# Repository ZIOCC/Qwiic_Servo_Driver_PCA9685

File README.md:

# Qwiic 16 Servo Driver (PCA9685)

> This product can be available for purchase [here](https://www.smart-prototyping.com/Zio-16-Servo-Controller.html).

#### Description

With the Zio 16-Channel 12 bit PWM controller, using the PCA9685 from NXP Semiconductors, you can control up to 16 servos or other PWM-controllable components using I2C.

Each output can be off or on (no PWM control), or set any channel to its own PWM frequency and duty cycle. The PCA9685 operates with a supply voltage range of 2.3v to 5.5v and both the inputs and outputs are 5.5v tolerant. Servos can be connected directly to output pins (up to 25 mA, 5.5v) or controlled with external drivers for more power-hungry applications. 

The board comes equipped with two Qwiic connectors to enable easy daisy-chaining. Need even more channels to control something like a hexapod robot? Quickly and easily connect another servo controller with the additional Qwiic connector and 6 solder-jumper configurable address bits. That means you can have up to 62 of these boards operating on the same I2C bus. You can also configure the boards to recognize group addresses, so that multiple boards can be controlled in parallel with a single command.

This is a derivative of Adafruit’s 16-Channel 12-bit PWM/Servo Driver - I2C interface - PCA9685, with the main difference being the addition of the Qwiic connectors. If you want to make Qwiic a regular part of your hardware hacking/making toolkit (we can’t image why you wouldn’t), this is the Servo Driver for you.

#### Specification

* 62 possible I2C addresses
* Weight: 8.0g (0.278oz)
* Dimension: 59.5x25.2 mm
* IC: PCA9685
* I2C address: 0x40-0x7F (default: 0x40)

#### Links

* [PCA9685 datasheet](https://www.smart-prototyping.com/image/data/NOA-RnD/101896%2016%20Servo%20Controller/PCA9685.pdf)
* [Adafruit PWM Servo Driver Library](https://github.com/adafruit/Adafruit-PWM-Servo-Driver-Library)
* [Example Code](https://www.smart-prototyping.com/image/data/NOA-RnD/101896%2016%20Servo%20Controller/2_servos.ino0)
* [Eagle files](https://github.com/ZIOCC/Qwiic_Servo_Driver_PCA9685)

Connections for Example Code, connecting two servos to the servo driver board. 

> ###### About Zio
> Zio is a new line of open sourced, compact, and grid layout boards, fully integrated for Arduino and Qwiic ecosystem. Designed ideally for wearables, robotics, small-space limitations or other on the go projects. Check out other awesome Zio products [here](https://www.smart-prototyping.com/Zio).

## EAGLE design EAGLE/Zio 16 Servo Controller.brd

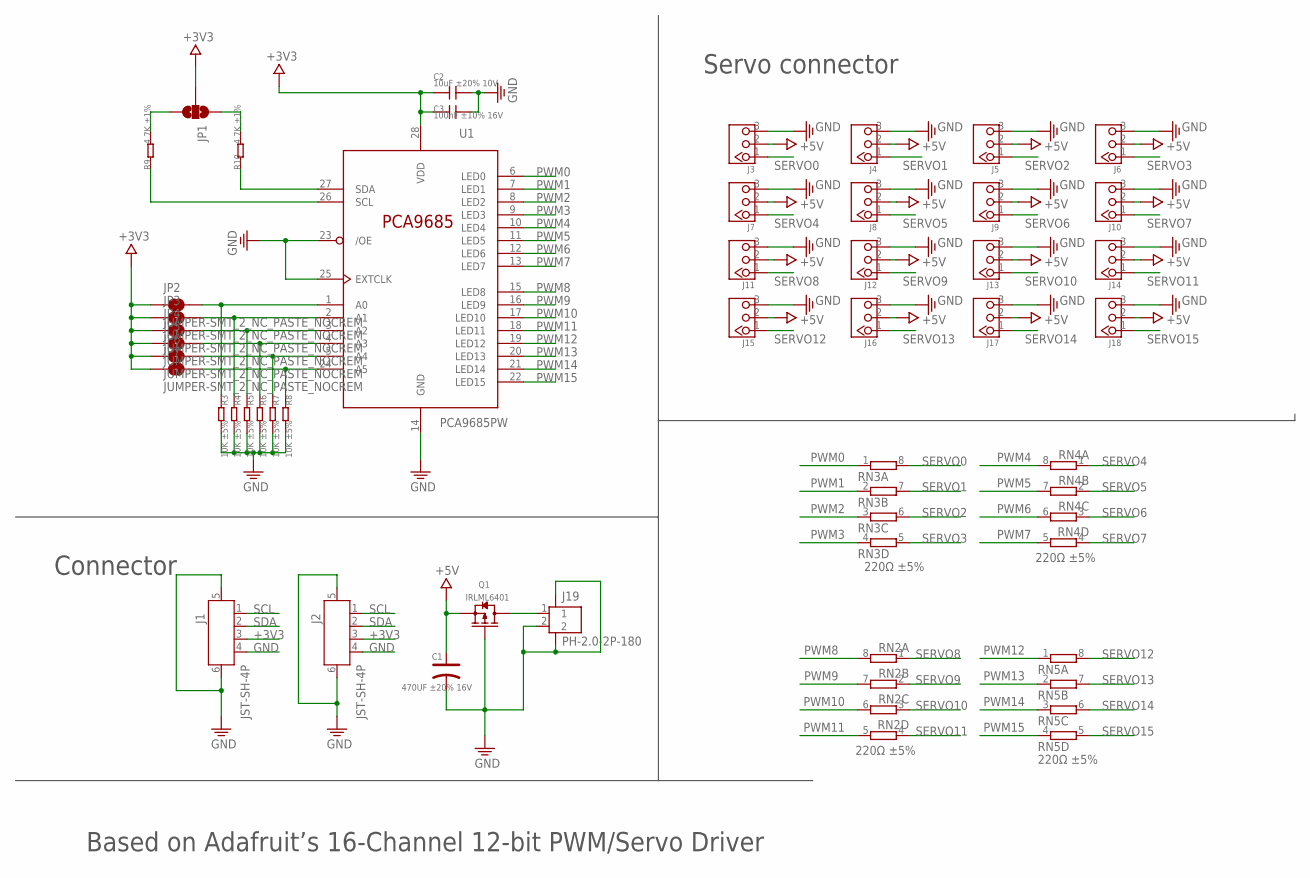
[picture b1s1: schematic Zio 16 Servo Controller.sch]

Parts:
C1: 470UF ±20% 16V; ELECTRO-SMD-E-7.8MM
C2: 10uF ±20% 10V; 0402
C3: 100nF ±10% 16V; 0402
J1, J2: JST-SH-4P; JST-SH-4P-90
J3, J4, J5, J6, J7, J8, J9, J10, J11, J12, J13, J14, J15, J16, J17, J18: HEADER-3P-2.54; 3P-2.54
J19: PH-2.0-2P-180; PH2.0_2P_180
JP1: JUMPER-SMT_3_2-NC_PASTE_NOCREM; SMT-JUMPER_3_2-NC_PASTE_SILK_NOCREM
JP2, JP3, JP4, JP5, JP6, JP7: JUMPER-SMT_2_NC_PASTE_NOCREM; SMT-JUMPER_2_NC_PASTE_SILK_NOCREM
Q1: IRLML6401; SOT23
R3, R4, R5, R6, R7, R8: 10K ±5%; 0402
R9, R10: 4.7K ±1%; 0402
RN2, RN3, RN4, RN5: 220Ω ±5%; RESISTOR-DIL_0603-ARV
U1: PCA9685PW; TSSOP28

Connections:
+3V3: C2.1, C3.1, J1.3, J2.3, JP1.2, JP2.1, JP3.1, JP4.1, JP5.1, JP6.1, JP7.1, U1.28 (VDD)
+5V: C1.+, J3.2, J4.2, J5.2, J6.2, J7.2, J8.2, J9.2, J10.2, J11.2, J12.2, J13.2, J14.2, J15.2, J16.2, J17.2, J18.2, Q1.2 (S)
GND: C1.-, C2.2, C3.2, J1.4, J1.5, J1.6, J2.4, J2.5, J2.6, J3.3, J4.3, J5.3, J6.3, J7.3, J8.3, J9.3, J10.3, J11.3, J12.3, J13.3, J14.3, J15.3, J16.3, J17.3, J18.3, J19.2, J19.3, J19.4, Q1.1 (G), R3.2, R4.2, R5.2, R6.2, R7.2, R8.2, U1.14 (GND), U1.23 (/OE), U1.25 (EXTCLK)
unnamed: JP2.2, R3.1, U1.1 (A0)
unnamed: JP3.2, R4.1, U1.2 (A1)
unnamed: JP4.2, R5.1, U1.3 (A2)
unnamed: JP5.2, R6.1, U1.4 (A3)
unnamed: JP6.2, R7.1, U1.5 (A4)
unnamed: JP7.2, R8.1, U1.24 (A5)
unnamed: J19.1, Q1.3 (D)
unnamed: JP1.3, R9.2
unnamed: JP1.1, R10.2
PWM0: RN3.1, U1.6 (LED0)
PWM1: RN3.2 (1), U1.7 (LED1)
PWM2: RN3.3 (1), U1.8 (LED2)
PWM3: RN3.4 (1), U1.9 (LED3)
PWM4: RN4.8 (2), U1.10 (LED4)
PWM5: RN4.7 (2), U1.11 (LED5)
PWM6: RN4.6 (2), U1.12 (LED6)
PWM7: RN4.5 (2), U1.13 (LED7)
PWM8: RN2.8 (2), U1.15 (LED8)
PWM9: RN2.7 (2), U1.16 (LED9)
PWM10: RN2.6 (2), U1.17 (LED10)
PWM11: RN2.5 (2), U1.18 (LED11)
PWM12: RN5.1, U1.19 (LED12)
PWM13: RN5.2 (1), U1.20 (LED13)
PWM14: RN5.3 (1), U1.21 (LED14)
PWM15: RN5.4 (1), U1.22 (LED15)
SCL: J1.1, J2.1, R9.1, U1.26 (SCL)
SDA: J1.2, J2.2, R10.1, U1.27 (SDA)
SERVO0: J3.1, RN3.8 (2)
SERVO1: J4.1, RN3.7 (2)
SERVO2: J5.1, RN3.6 (2)
SERVO3: J6.1, RN3.5 (2)
SERVO4: J7.1, RN4.1
SERVO5: J8.1, RN4.2 (1)
SERVO6: J9.1, RN4.3 (1)
SERVO7: J10.1, RN4.4 (1)
SERVO8: J11.1, RN2.1
SERVO9: J12.1, RN2.2 (1)
SERVO10: J13.1, RN2.3 (1)
SERVO11: J14.1, RN2.4 (1)
SERVO12: J15.1, RN5.8 (2)
SERVO13: J16.1, RN5.7 (2)
SERVO14: J17.1, RN5.6 (2)
SERVO15: J18.1, RN5.5 (2)

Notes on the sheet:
Servo connector
Connector
Based on Adafruit’s 16-Channel 12-bit PWM/Servo Driver

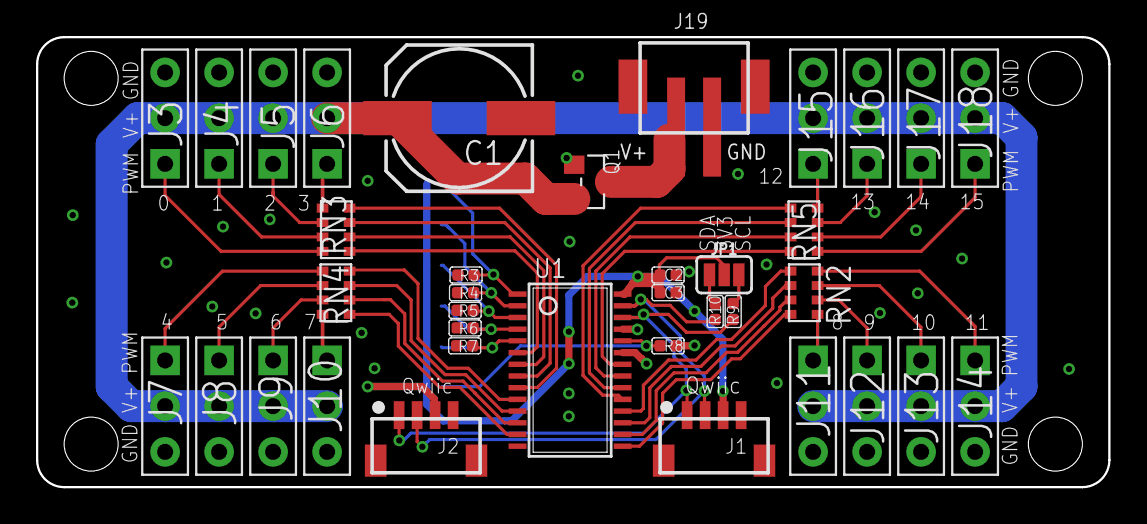
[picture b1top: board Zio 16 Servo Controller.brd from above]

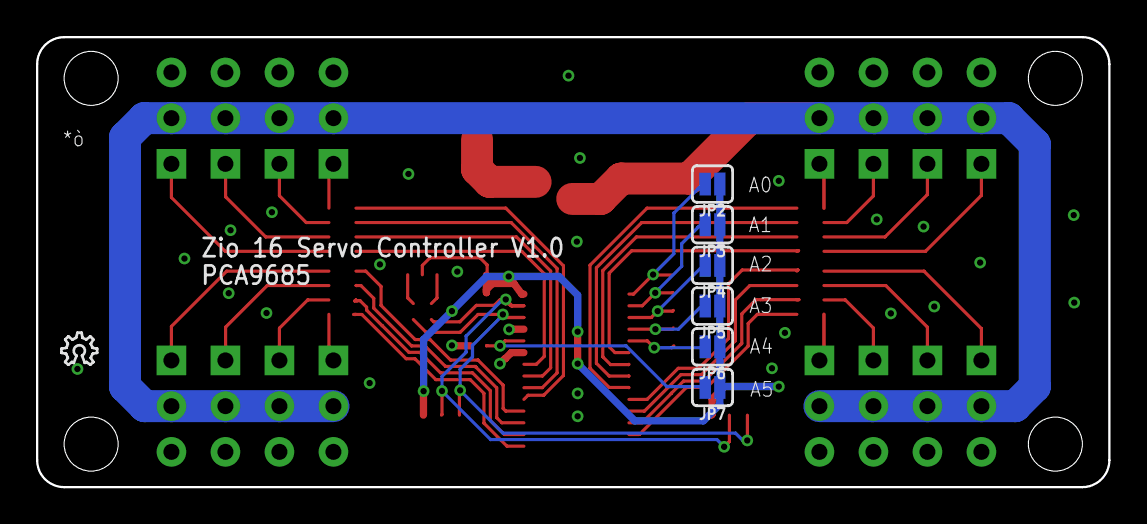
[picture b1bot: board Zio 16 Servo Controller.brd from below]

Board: 2 copper layers, 59.6 x 25.0 mm, 46 parts (8 on the bottom side), 46 nets.

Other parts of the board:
E$4: 7MM
LOGO1: LOGO-OSHW-6MILX0070-NT; OSHW_6X70_NOTEXT
U$21: 6MM
